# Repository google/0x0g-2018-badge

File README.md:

## About ##

This is the electronic badge distributed at 0x0G, Google's annual event at
DEF CON/Black Hat.  This badge features a PIC microcontroller driving a ring of
LEDs with communication over infrared.

Included are circuit design files and firmware source.  Both are licensed under
the Apache 2 license.

This is not an officially supported Google product.  This is a one-time release,
do not expect updates even if it turns out we have bugs.

## Authors ##

If you have any questions about the badge, feel free to contact one of the
creators:

- matir@google.com
- jsonp@google.com
- claymore@google.com

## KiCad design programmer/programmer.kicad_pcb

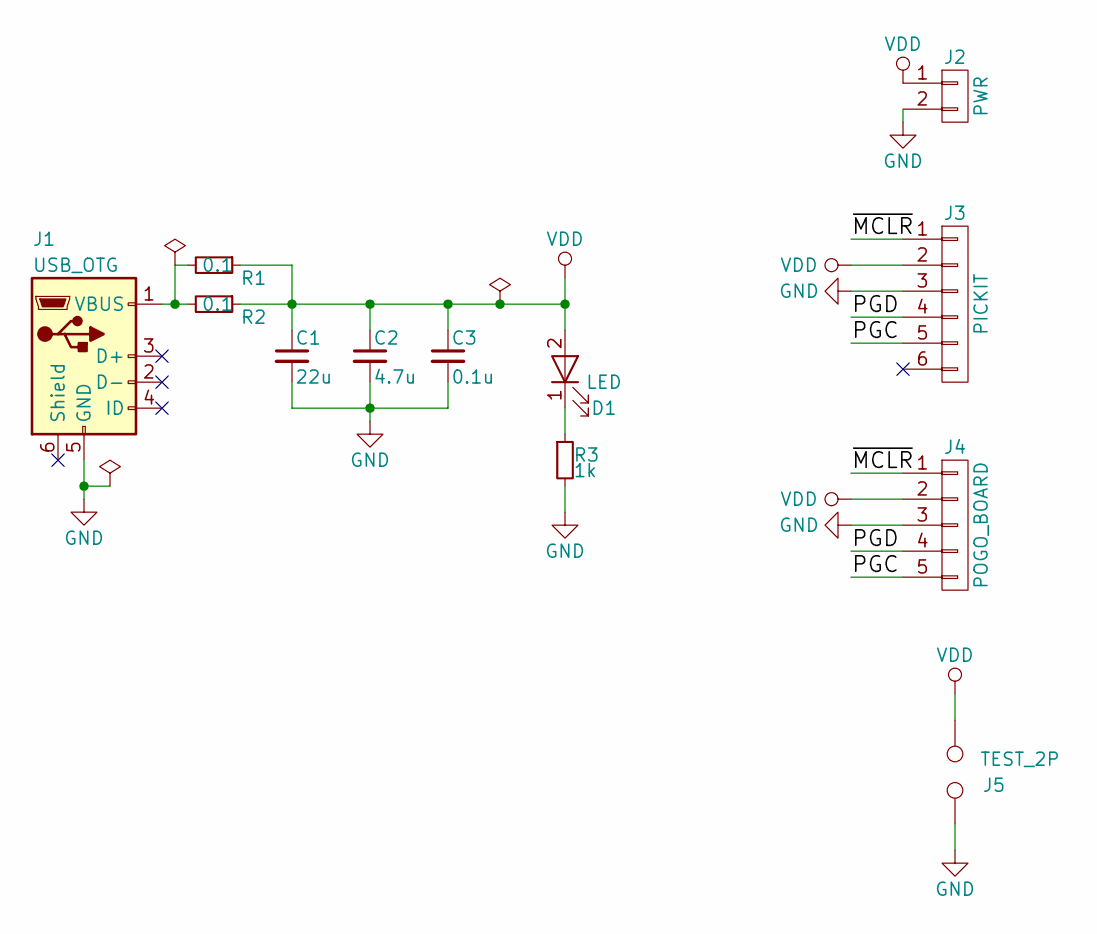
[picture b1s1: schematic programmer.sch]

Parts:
C1: 22u; C_1206_HandSoldering
C2: 4.7u; C_1206_HandSoldering
C3: 0.1u; C_1206_HandSoldering
D1: LED; LED_0805_HandSoldering
J1: USB_OTG; USB_Micro-B_Amphenol_10103594-0001LF_Horizontal
J2: PWR; Pin_Header_Angled_1x02_Pitch2.54mm
J3: PICKIT; Pin_Header_Angled_1x06_Pitch2.54mm
J4: POGO_BOARD; Pin_Header_Straight_1x05_Pitch2.54mm
J5: TEST_2P; Test_Point_2Pads
R1, R2: 0.1; R_1206_HandSoldering
R3: 1k; R_0805_HandSoldering

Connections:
/PGC: J3.5, J4.5
/PGD: J3.4, J4.4
/~MCLR: J3.1, J4.1
GND: C1.2, C2.2, C3.2, J1.5 (GND), J2.2, J3.3, J4.3, J5.2, R3.2
unnamed: D1.1 (K), R3.1
unnamed: J1.1 (VBUS), R1.2, R2.2
VDD: C1.1, C2.1, C3.1, D1.2 (A), J2.1, J3.2, J4.2, J5.1, R1.1, R2.1

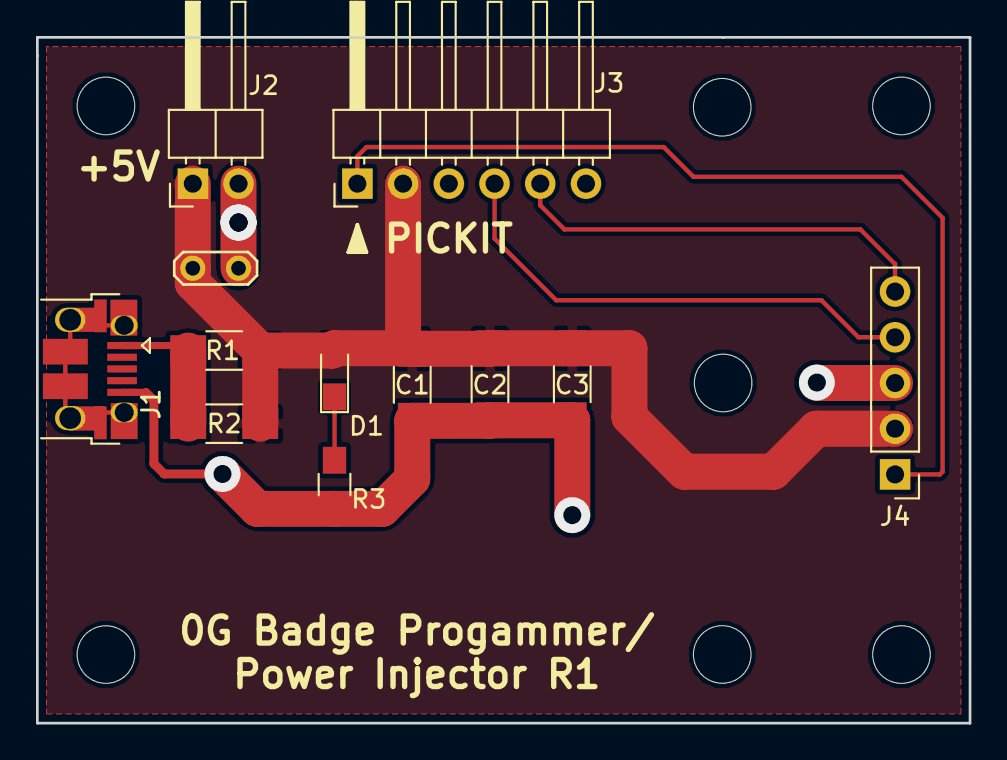
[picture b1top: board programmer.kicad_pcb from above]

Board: 2 copper layers, 51.8 x 38.1 mm, 12 parts (0 on the bottom side), 7 nets.

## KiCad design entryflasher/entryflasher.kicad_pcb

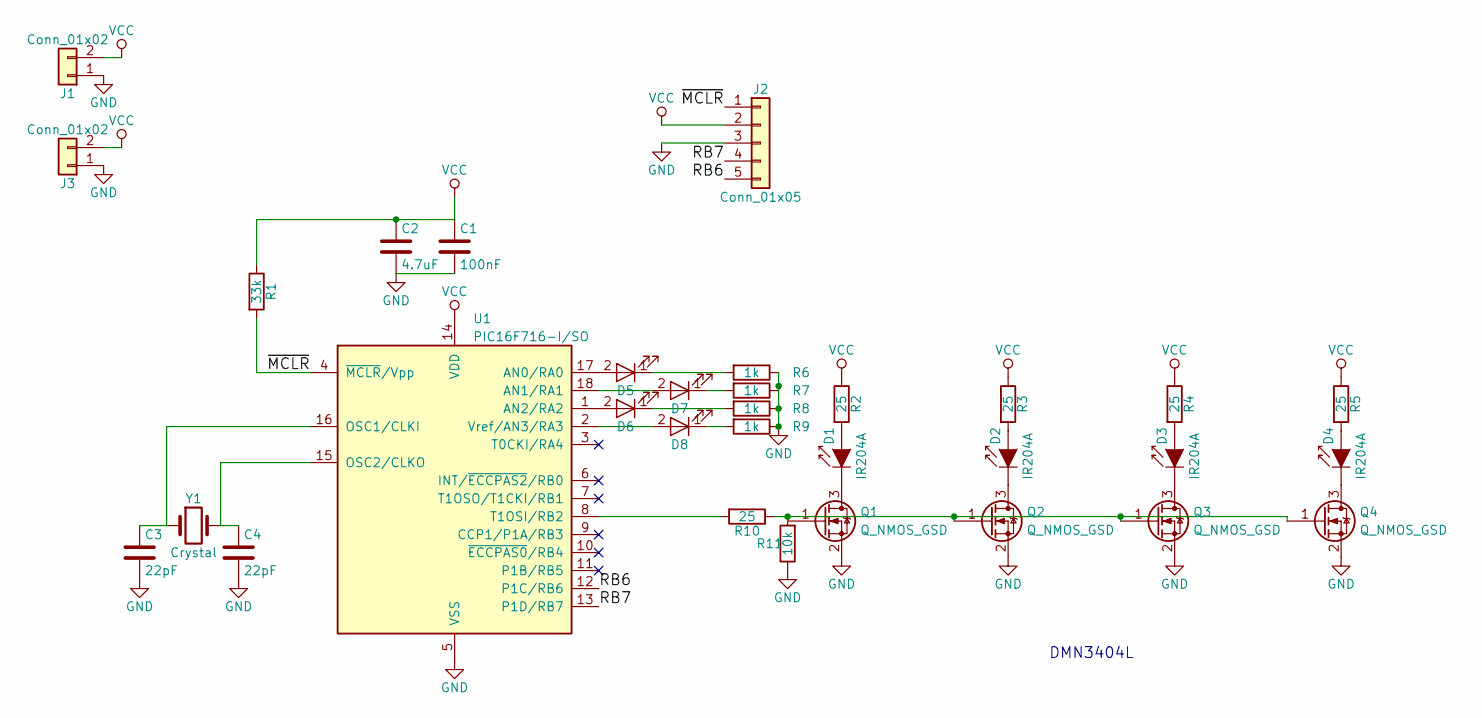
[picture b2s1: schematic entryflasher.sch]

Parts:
C1: 100nF; C_0805_HandSoldering
C2: 4.7uF; C_0805_HandSoldering
C3, C4: 22pF; C_0805_HandSoldering
D1, D2, D3, D4: IR204A; LED-3MM
D5, D6, D7, D8: LED; LED_0805_HandSoldering
J1, J3: Conn_01x02; Pin_Header_Straight_1x02
J2: Conn_01x05; Pin_Header_Straight_1x05
Q1, Q2, Q3, Q4: Q_NMOS_GSD; SOT-23_Handsoldering
R1: 33k; R_0805_HandSoldering
R2, R3, R4, R5, R10: 25; R_0805_HandSoldering
R6, R7, R8, R9: 1k; R_0805_HandSoldering
R11: 10k; R_0805_HandSoldering
U1: PIC16F716-I/SO; SOIC-18W_7.5x11.6mm_Pitch1.27mm
Y1: Crystal; ABLS-4MHZ-B2-T

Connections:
/RB6: J2.5, U1.12 (P1C/RB6)
/RB7: J2.4, U1.13 (P1D/RB7)
/~MCLR: J2.1, R1.2, U1.4 (~MCLR~/Vpp)
GND: C1.2, C2.2, C3.2, C4.2, J1.1, J2.3, J3.1, Q1.2 (S), Q2.2 (S), Q3.2 (S), Q4.2 (S), R6.1, R7.1, R8.1, R9.1, R11.1, U1.5 (VSS)
unnamed: C3.1, U1.16 (OSC1/CLKI), Y1.1
unnamed: C4.1, U1.15 (OSC2/CLKO), Y1.2
unnamed: D1.1 (K), Q1.3 (D)
unnamed: D1.2 (A), R2.2
unnamed: D2.1 (K), Q2.3 (D)
unnamed: D2.2 (A), R3.2
unnamed: D3.1 (K), Q3.3 (D)
unnamed: D3.2 (A), R4.2
unnamed: D4.1 (K), Q4.3 (D)
unnamed: D4.2 (A), R5.2
unnamed: D5.1 (K), R6.2
unnamed: D5.2 (A), U1.17 (AN0/RA0)
unnamed: D6.1 (K), R8.2
unnamed: D6.2 (A), U1.1 (AN2/RA2)
unnamed: D7.1 (K), R7.2
unnamed: D7.2 (A), U1.18 (AN1/RA1)
unnamed: D8.1 (K), R9.2
unnamed: D8.2 (A), U1.2 (Vref/AN3/RA3)
unnamed: Q1.1 (G), Q2.1 (G), Q3.1 (G), Q4.1 (G), R10.1, R11.2
unnamed: R10.2, U1.8 (T1OSI/RB2)
VCC: C1.1, C2.1, J1.2, J2.2, J3.2, R1.1, R2.1, R3.1, R4.1, R5.1, U1.14 (VDD)

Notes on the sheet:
DMN3404L

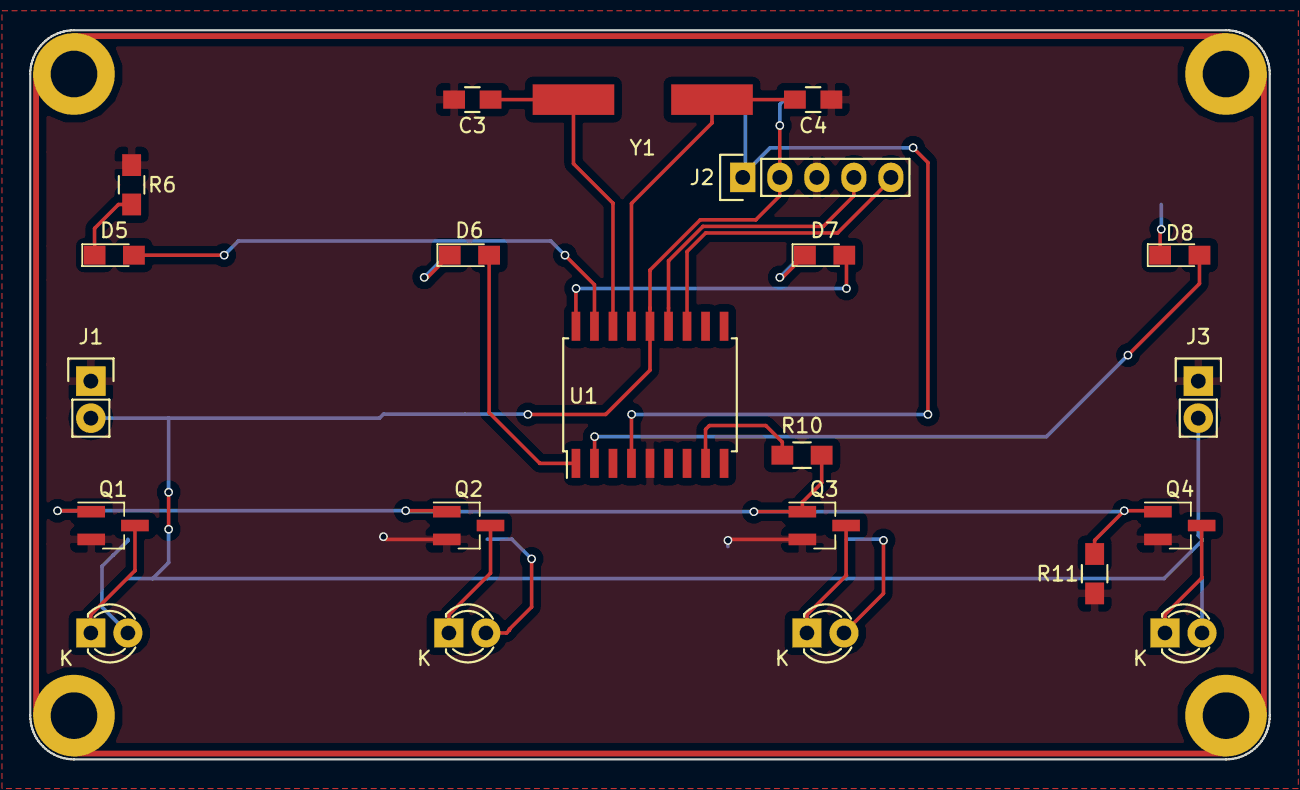
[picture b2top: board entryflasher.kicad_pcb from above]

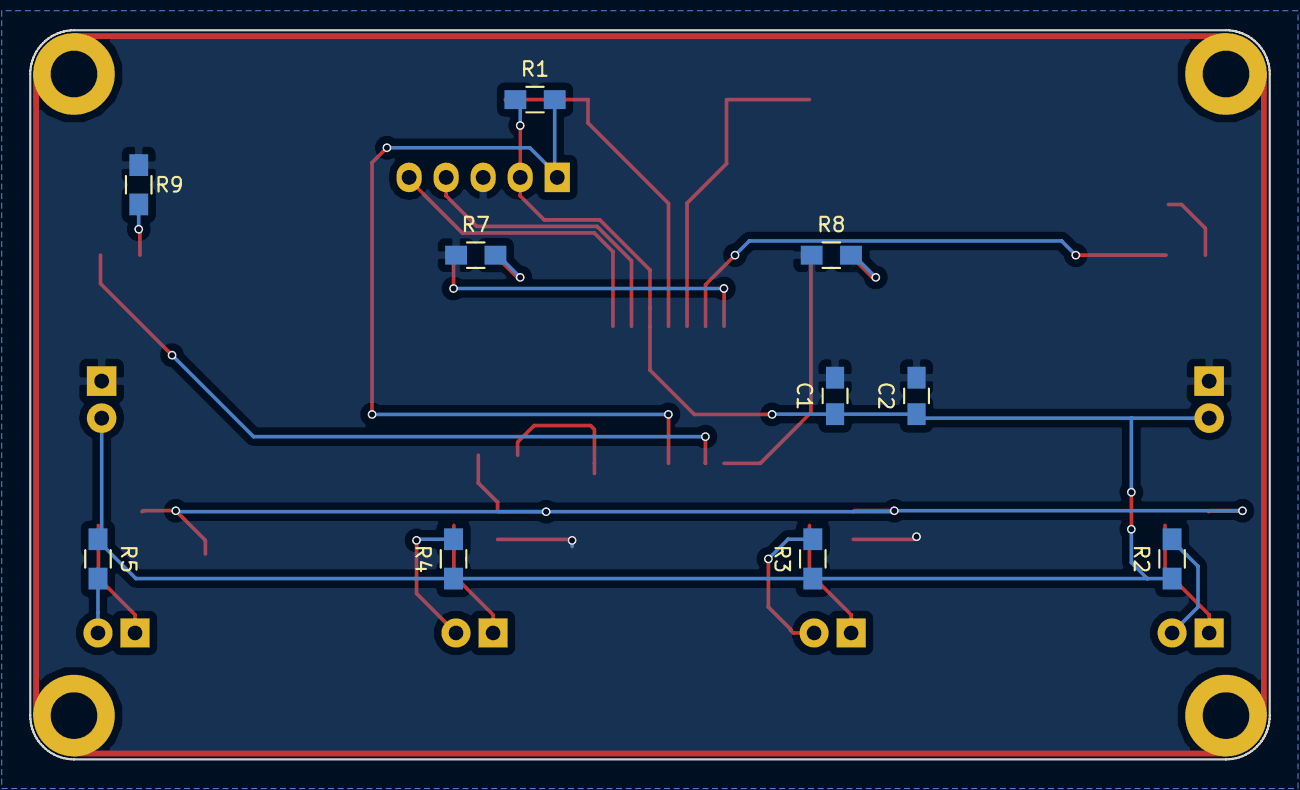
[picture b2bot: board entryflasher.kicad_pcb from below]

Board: 2 copper layers, 85.0 x 50.0 mm, 32 parts (10 on the bottom side), 25 nets.

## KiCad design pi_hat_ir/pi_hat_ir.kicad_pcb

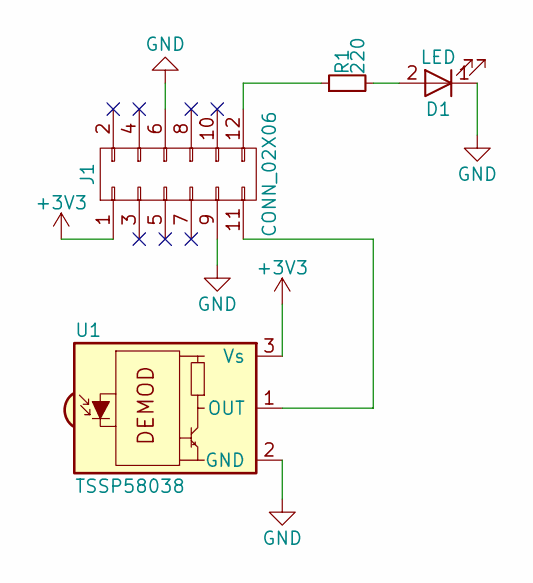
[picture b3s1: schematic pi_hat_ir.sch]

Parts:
D1: LED; LED_D3.0mm
J1: CONN_02X06; Pin_Header_Straight_2x06_Pitch2.54mm
R1: 220; R_0805_HandSoldering
U1: TSSP58038; IRReceiver_Vishay_MINICAST-3pin

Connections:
+3V3: J1.1, U1.3 (Vs)
GND: D1.1 (K), J1.6, J1.9, U1.2 (GND)
unnamed: D1.2 (A), R1.2
unnamed: J1.11, U1.1 (OUT)
unnamed: J1.12, R1.1

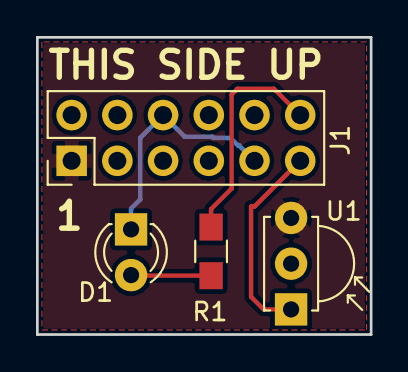
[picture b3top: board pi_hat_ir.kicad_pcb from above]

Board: 2 copper layers, 18.5 x 16.5 mm, 4 parts (0 on the bottom side), 5 nets.

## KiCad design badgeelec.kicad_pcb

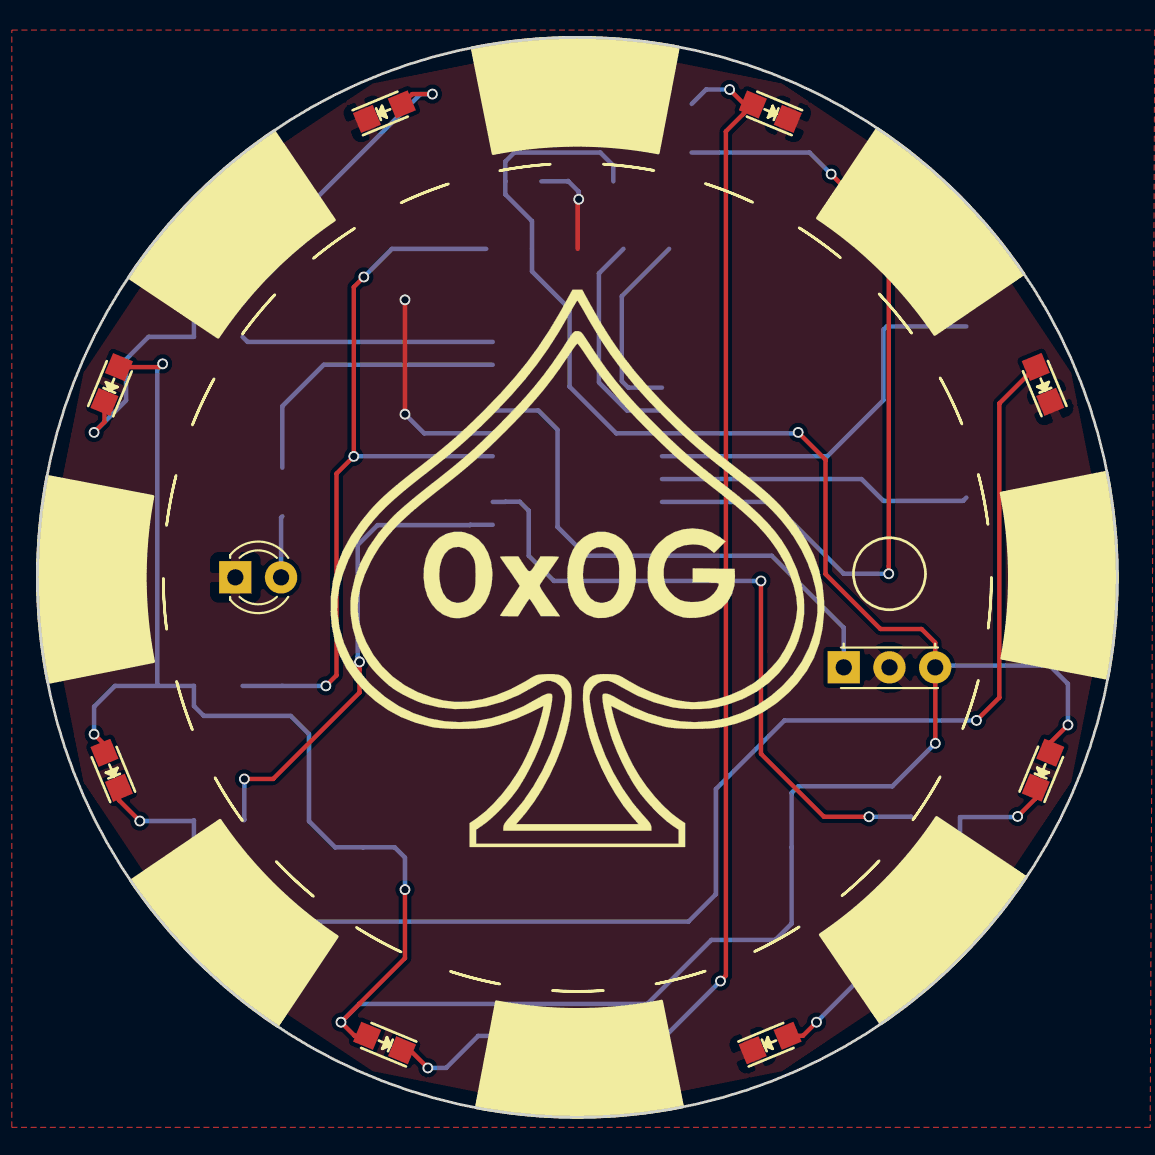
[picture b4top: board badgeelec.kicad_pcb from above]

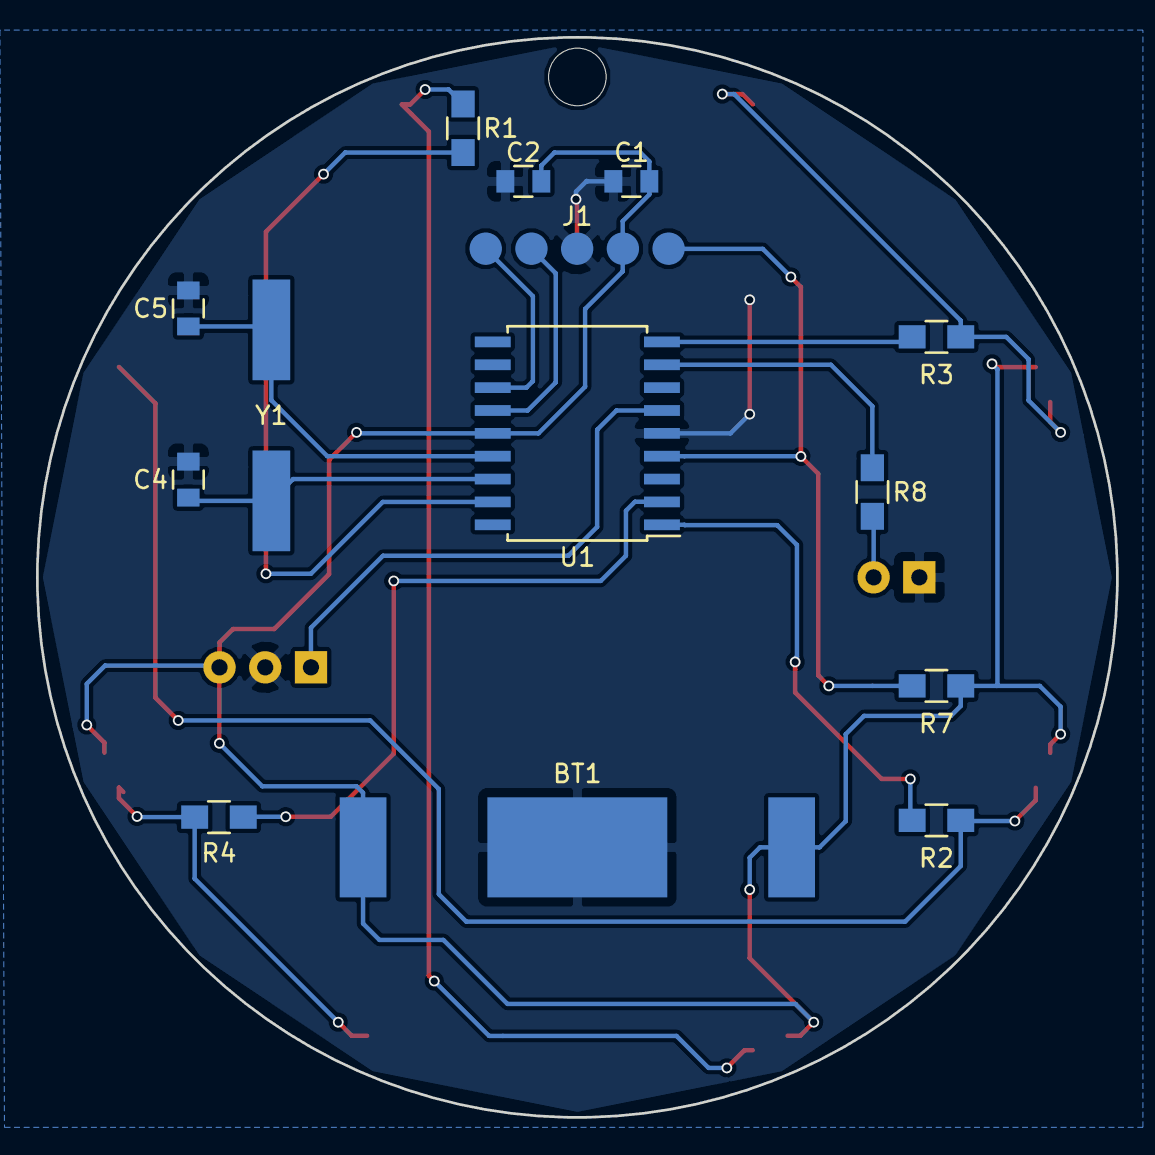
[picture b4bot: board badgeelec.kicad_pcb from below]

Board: 2 copper layers, 60.0 x 60.0 mm, 24 parts (14 on the bottom side), 18 nets.

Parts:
BT1: Battery_Cell; BC-2003-TR
C1: 100nF; C_0805
C2: 1uF; C_0805
C4, C5: 18pF; C_0805
D1, D2, D3, D4, D5, D6, D7, D8: LED; LED_0805
D9: IR LED; LED_D3.0mm
J1: PROG_CONN; SMD_PROG_5
R1: 1k; R_0805_HandSoldering
R2: 430; R_0805_HandSoldering
R3, R4, R8: 220; R_0805_HandSoldering
R7: 33K; R_0805_HandSoldering
U1: PIC16F716-I-SO-ND; SOIC-18W_7.5x11.6mm_Pitch1.27mm
U2: TSSP58038; tssp58038_flat
Y1: 4Mhz; ABLS-4MHZ-B2-T

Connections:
/RA0: R1.2, U1.17
/RA2: R2.2, U1.1
/RA3: R4.2, U1.2
/RB2: R8.1, U1.8
/RB3: R3.2, U1.9
/RB6: J1.5, U1.12
/RB7: J1.4, U1.13
/~MCLR: J1.1, R7.2, U1.4
GND: BT1.2, C1.2, C2.2, C4.2, C5.2, D3.1, D4.1, D7.1, D8.1, D9.1, J1.3, U1.5, U2.2
unnamed: C4.1, U1.16, Y1.1
unnamed: C5.1, U1.15, Y1.2
unnamed: D1.1, D3.2, R1.1
unnamed: D2.1, D4.2, R3.1
unnamed: D5.1, D7.2, R2.1
unnamed: D6.1, D8.2, R4.1
unnamed: D9.2, R8.2
unnamed: U1.6, U2.1
VDD: BT1.1, C1.1, C2.1, D1.2, D2.2, D5.2, D6.2, J1.2, R7.1, U1.14, U2.3

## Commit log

2018-03-09 prototype r1
2018-03-09 add gerbers for prototype r1
2018-03-12 Added more BOM detail
2018-03-28 additional details
2018-04-09 Halfway through v2
2018-04-10 Implemented prototypev2
2018-04-23 Schematic for final layout prototype 1
2018-04-23 Start working on layout for final prototype 1
2018-04-23 Start working on generator to produce graphics footprint
2018-04-24 Fix issues with generating the guides where left and right sides were not the same
2018-04-25 Created/changed IR receiver to horizontal footprint, implemented basic generator for poker-chip style layout
2018-04-25 Done layout for proto final v1
2018-04-25 Routed prototype final v1
2018-04-26 Create gerbers for r2
2018-04-26 Forgot prototype silkS module
2018-04-26 check in gerber zip
2018-05-03 Cut revision 3
2018-05-03 Cut r4
2018-05-07 First pass verifying everything
2018-05-09 Add programmer and PI IR Hat.
2018-05-09 Fix missing trace.
2018-05-16 Start work on firmware.
2018-05-16 Add LED blinking based on jsonp@s code.
2018-05-16 Add engineering instructions
2018-05-16 Add solder paste instructions
2018-05-16 Uploadable firmware.
2018-05-19 IR decoder work.
2018-05-19 Fix ir_decoder.c
2018-05-19 Fully working decoder.
2018-06-04 Generate X-Y files
2018-06-11 Refactor LED control, fix LED clear
2018-06-11 Implement flashing modes for LED
2018-07-05 Preparing for release v1.
2018-07-05 Add copyright headers.
2018-07-05 Fix company name.
2018-07-05 Update programmer
2018-07-05 Clean up release warnings.
2018-07-05 Add a README.
2018-07-09 Update graphics.
2018-07-10 Add pokerchip graphic.
2018-07-10 Add some code to transmit a mark.
2018-07-11 First pass of full IR transmitter.
2018-07-11 Fix timing.
2018-07-11 Add entryflasher PCB to repo
2018-07-17 Ignore build.
2018-07-17 Add other compiler outputs.
2018-07-17 Remove compiler outputs.
2018-07-17 Fix NEC transmission with EOM marker.
2018-07-18 Implement new LED modes
2018-07-18 badge mode is now selectable from IR remote
2018-07-18 pound define constant remote codes
2018-07-18 Startup mode is now chase 2
2018-07-18 Shut down IR decode subsystem when the badge is set to one of the 4 googler teams
2018-07-18 MVP done :D
2018-07-18 Clean up some magic constants
2018-07-18 Add REDBLUE flash mode
2018-07-20 Only output IR debug if define is set.
2018-07-20 Change participant mode.
2018-07-20 Synchronize!
2018-07-31 Bump readme.
